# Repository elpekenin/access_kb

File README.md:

---
⚠️ _This file contains some icons that should render on GitHub, but **don't worry!** if they don't_

📝 While all the source and documentation I've developed is written on English, the report is on Spanish to be presented at my University, I might translate it on the future

---

Access keyboard
===============
This project's goal is to make a highly customizable keyboard with a bunch of accessibility add-ons, so that **most** people can use it.

File structure:
```
📂 access_kb
├─ 📂firmware/     - Code running on the keyboard, compiled using qmk_build
├─ 📂hardware/     - PCB files
|  └─ 📂libraries/     * References to KiCAD symbols and footprints 
├─ 📂software      - Client running on the PC to control the keyboard
└─ 📂typst        - Sources used to create the PDF report
```

Firmware
========
Firmware made using [QMK](https://github.com/qmk/qmk_firmware).

Code and patches can be seen on [qmk_userspace](https://github.com/elpekenin/qmk_userspace), it is built using [qmk_build](https://github.com/elpekenin/qmk_build)

Hardware
========
The PCB was designed with KiCAD, based on ***Raspberry Pi Pico*** development board, and using some symbol/footprint libraries:
- [marbastlib](https://github.com/ebastler/marbastlib) -- Keyboard parts
- [rp-pico](https://github.com/ncarandini/KiCad-RP-Pico/) -- Raspberry Pi Pico
- [custom](./hardware/libraries/my_components.pretty/)
   - Screen models based on 1xN female 2.54mm pin connectors + roughly measured rectangles. Used for placing and sizing, not used in final model
   - Symbol for MC74HC589ADR2G, footprint is just a 16-pin SOIC

Features:
- Split
- Ortholinear
- Shift registers to reduce the pins needed
  - PISO for matrix scanning
  - SIPO for control signals
- Unused GPIO's are broken out so they be used too
- e-Ink display to show the current configuration

Software 
========
Program using [Vue](https://vuejs.org/) and [Tauri](https://tauri.app/) on your computer, that can control some features of the keyboard and send information. Based on [KarlK90's work](https://github.com/qmk/qmk_xap)

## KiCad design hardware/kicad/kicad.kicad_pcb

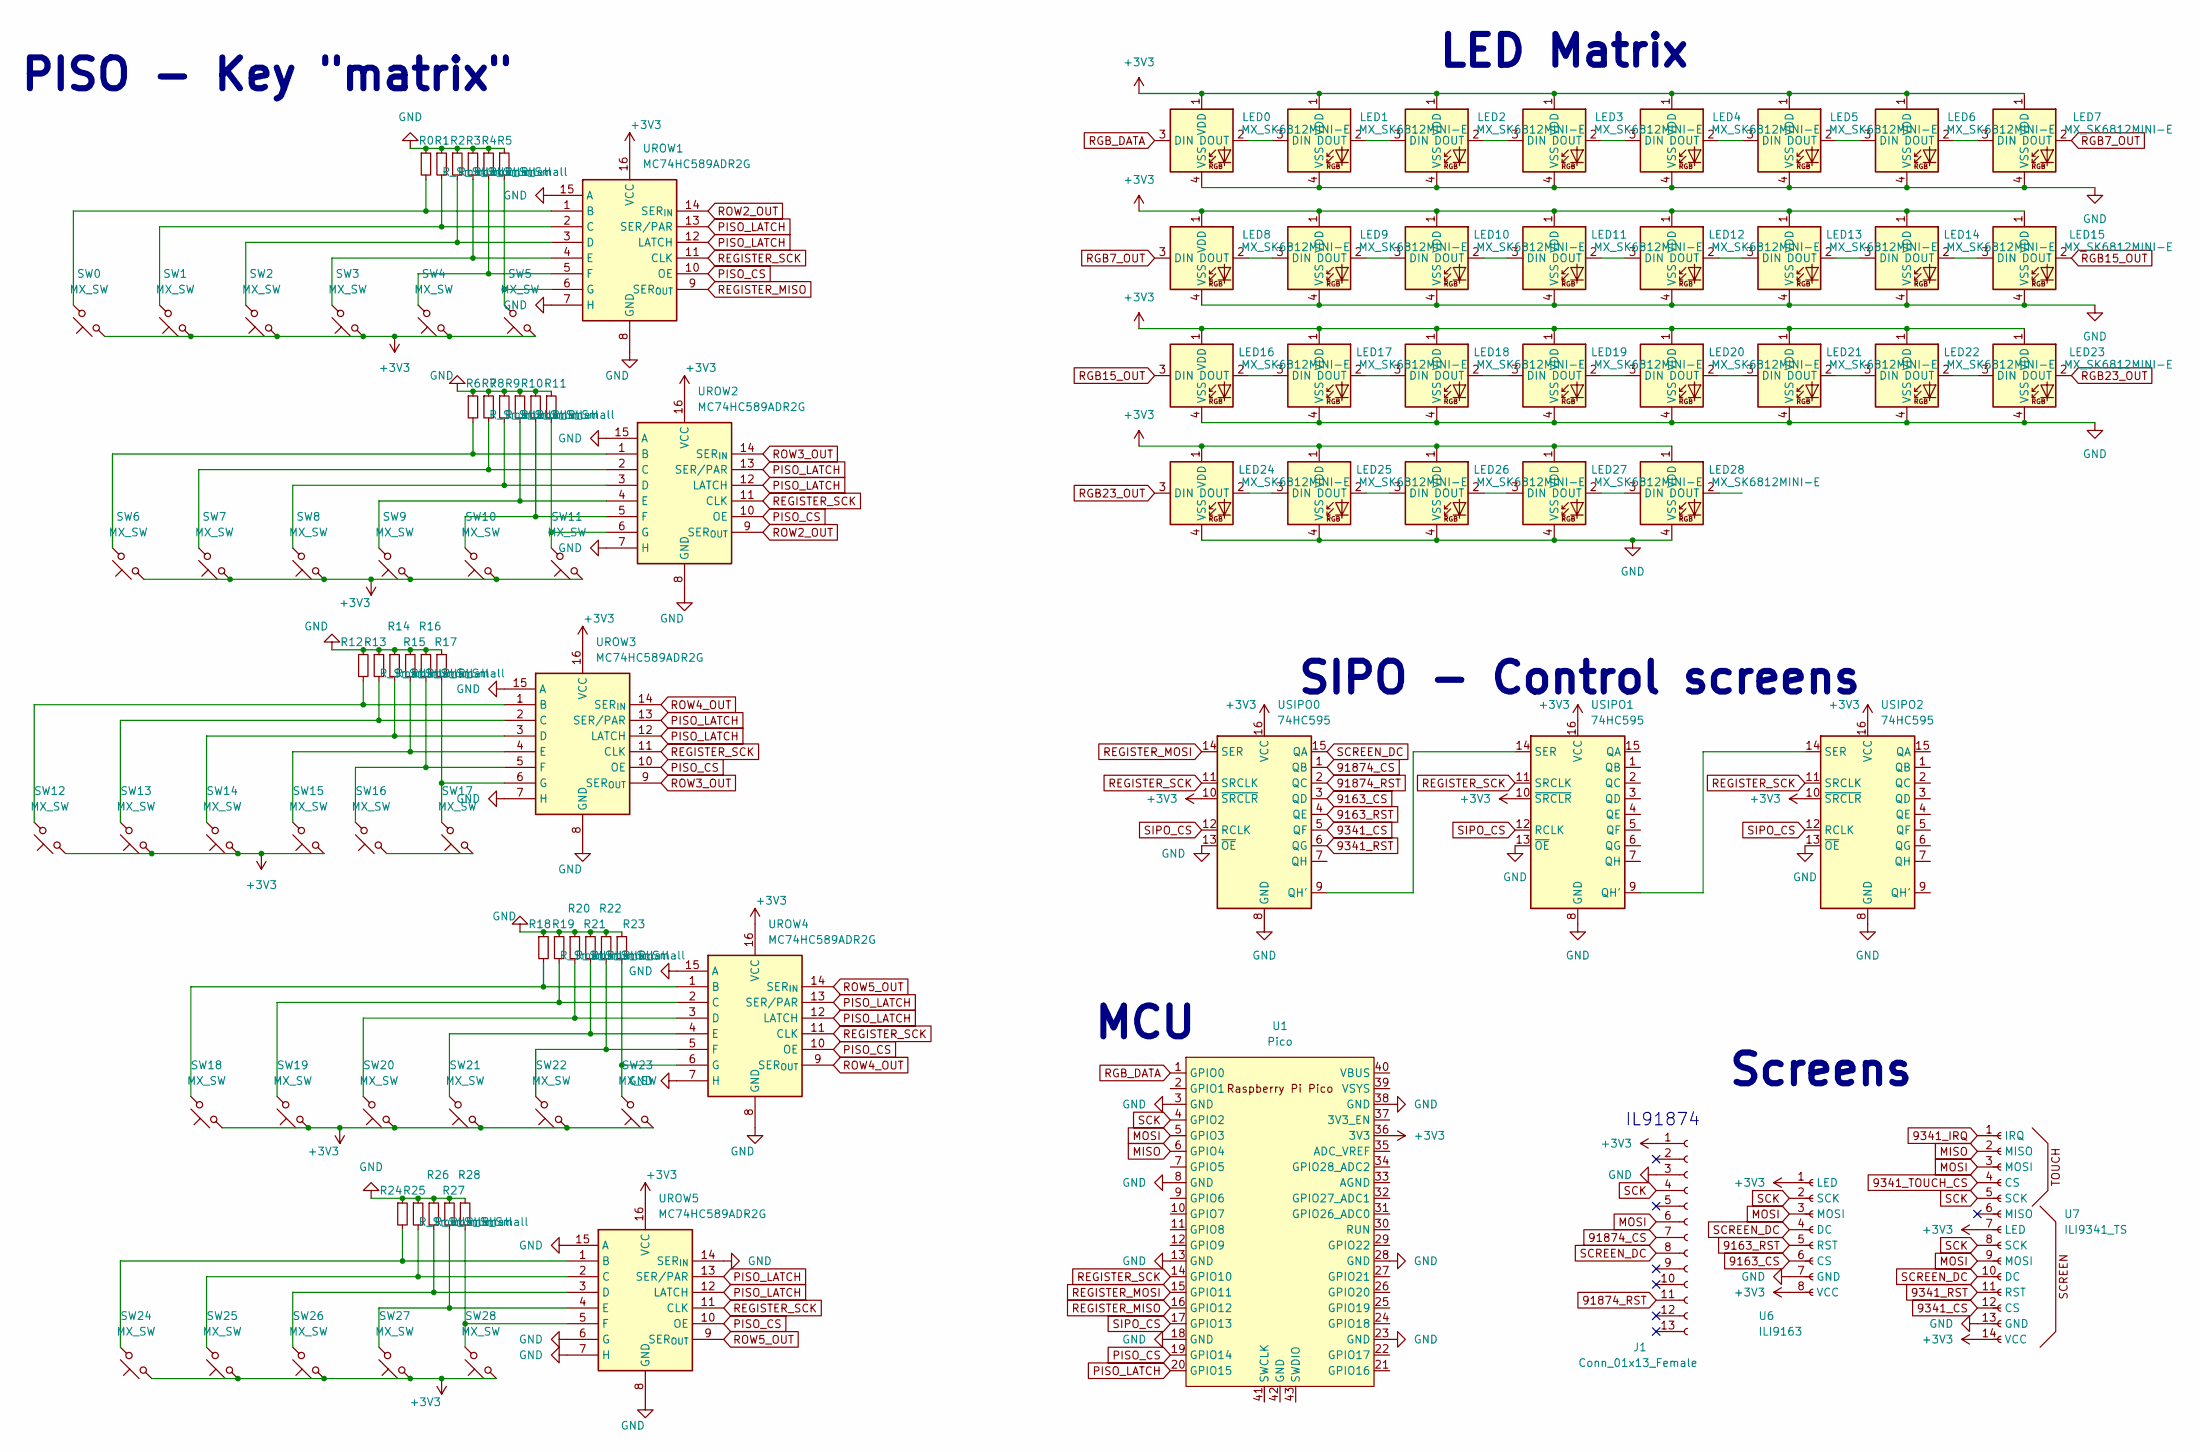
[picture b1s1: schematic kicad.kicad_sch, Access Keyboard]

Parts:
J1: Conn_01x13_Female; PinHeader_1x13_P1.00mm_Vertical
LED0, LED1, LED2, LED3, LED4, LED5, LED6, LED7, LED8, LED9, LED10, LED11, LED12, LED13, LED14, LED15, LED16, LED17, LED18, LED19, LED20, LED21, LED22, LED23, LED24, LED25, LED26, LED27, LED28: MX_SK6812MINI-E; LED_MX_6028R
R0, R1, R2, R3, R4, R5, R6, R7, R8, R9, R10, R11, R12, R13, R14, R15, R16, R17, R18, R19, R20, R21, R22, R23, R24, R25, R26, R27, R28: R_Small; R_1206_3216Metric_Pad1.30x1.75mm_HandSolder
SW0, SW1, SW2, SW3, SW4, SW5, SW6, SW7, SW8, SW9, SW10, SW11, SW12, SW13, SW14, SW15, SW16, SW17, SW18, SW19, SW20, SW21, SW22, SW23, SW24, SW25, SW26, SW27, SW28: MX_SW; SW_MX_1u
U1: Pico; RPi_Pico_SMD_TH
U6: ILI9163
U7: ILI9341_TS
UROW1, UROW2, UROW3, UROW4, UROW5: MC74HC589ADR2G; SO-16_3.9x9.9mm_P1.27mm
USIPO0, USIPO1, USIPO2: 74HC595; SO-16_3.9x9.9mm_P1.27mm

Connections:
9163_CS: U6.6 (CS), USIPO0.3 (QD)
9163_RST: U6.5 (RST), USIPO0.4 (QE)
9341_CS: U7.12 (CS), USIPO0.5 (QF)
9341_IRQ: U7.1 (IRQ)
9341_RST: U7.11 (RST), USIPO0.6 (QG)
9341_TOUCH_CS: U7.4 (CS)
91874_CS: J1.7, USIPO0.1 (QB)
91874_RST: J1.11, USIPO0.2 (QC)
+3V3: J1.1, LED0.1 (VDD), LED1.1 (VDD), LED2.1 (VDD), LED3.1 (VDD), LED4.1 (VDD), LED5.1 (VDD), LED6.1 (VDD), LED7.1 (VDD), LED8.1 (VDD), LED9.1 (VDD), LED10.1 (VDD), LED11.1 (VDD), LED12.1 (VDD), LED13.1 (VDD), LED14.1 (VDD), LED15.1 (VDD), LED16.1 (VDD), LED17.1 (VDD), LED18.1 (VDD), LED19.1 (VDD), LED20.1 (VDD), LED21.1 (VDD), LED22.1 (VDD), LED23.1 (VDD), LED24.1 (VDD), LED25.1 (VDD), LED26.1 (VDD), LED27.1 (VDD), LED28.1 (VDD), SW0.1, SW1.1, SW2.1, SW3.1, SW4.1, SW5.1, SW6.1, SW7.1, SW8.1, SW9.1, SW10.1, SW11.1, SW12.1, SW13.1, SW14.1, SW15.1, SW18.1, SW19.1, SW20.1, SW21.1, SW22.1, SW23.1, SW24.1, SW25.1, SW26.1, SW27.1, SW28.1, U1.36 (3V3), U6.1 (LED), U6.8 (VCC), U7.7 (LED), U7.14 (VCC), UROW1.16 (VCC), UROW2.16 (VCC), UROW3.16 (VCC), UROW4.16 (VCC), UROW5.16 (VCC), USIPO0.10 (~SRCLR), USIPO0.16 (VCC), USIPO1.10 (~SRCLR), USIPO1.16 (VCC), USIPO2.10 (~SRCLR), USIPO2.16 (VCC)
GND: J1.3, LED0.4 (VSS), LED1.4 (VSS), LED2.4 (VSS), LED3.4 (VSS), LED4.4 (VSS), LED5.4 (VSS), LED6.4 (VSS), LED7.4 (VSS), LED8.4 (VSS), LED9.4 (VSS), LED10.4 (VSS), LED11.4 (VSS), LED12.4 (VSS), LED13.4 (VSS), LED14.4 (VSS), LED15.4 (VSS), LED16.4 (VSS), LED17.4 (VSS), LED18.4 (VSS), LED19.4 (VSS), LED20.4 (VSS), LED21.4 (VSS), LED22.4 (VSS), LED23.4 (VSS), LED24.4 (VSS), LED25.4 (VSS), LED26.4 (VSS), LED27.4 (VSS), LED28.4 (VSS), R0.1, R1.1, R2.1, R3.1, R4.1, R5.1, R6.1, R7.1, R8.1, R9.1, R10.1, R11.1, R12.1, R13.1, R14.1, R15.1, R16.1, R17.1, R18.1, R19.1, R20.1, R21.1, R22.1, R23.1, R24.1, R25.1, R26.1, R27.1, R28.1, U1.3 (GND), U1.8 (GND), U1.13 (GND), U1.18 (GND), U1.23 (GND), U1.28 (GND), U1.38 (GND), U6.7 (GND), U7.13 (GND), UROW1.7 (H), UROW1.8 (GND), UROW1.15 (A), UROW2.7 (H), UROW2.8 (GND), UROW2.15 (A), UROW3.7 (H), UROW3.8 (GND), UROW3.15 (A), UROW4.7 (H), UROW4.8 (GND), UROW4.15 (A), UROW5.6 (G), UROW5.7 (H), UROW5.8 (GND), UROW5.14 (SER_{IN}), UROW5.15 (A), USIPO0.8 (GND), USIPO0.13 (~OE), USIPO1.8 (GND), USIPO1.13 (~OE), USIPO2.8 (GND), USIPO2.13 (~OE)
MISO: U1.6 (GPIO4), U7.2 (MISO)
MOSI: J1.6, U1.5 (GPIO3), U6.3 (MOSI), U7.3 (MOSI), U7.9 (MOSI)
unnamed: LED0.2 (DOUT), LED1.3 (DIN)
unnamed: LED1.2 (DOUT), LED2.3 (DIN)
unnamed: LED2.2 (DOUT), LED3.3 (DIN)
unnamed: LED3.2 (DOUT), LED4.3 (DIN)
unnamed: LED4.2 (DOUT), LED5.3 (DIN)
unnamed: LED5.2 (DOUT), LED6.3 (DIN)
unnamed: LED6.2 (DOUT), LED7.3 (DIN)
unnamed: LED8.2 (DOUT), LED9.3 (DIN)
unnamed: LED10.2 (DOUT), LED11.3 (DIN)
unnamed: LED9.2 (DOUT), LED10.3 (DIN)
unnamed: LED11.2 (DOUT), LED12.3 (DIN)
unnamed: LED12.2 (DOUT), LED13.3 (DIN)
unnamed: LED13.2 (DOUT), LED14.3 (DIN)
unnamed: LED14.2 (DOUT), LED15.3 (DIN)
unnamed: LED16.2 (DOUT), LED17.3 (DIN)
unnamed: LED17.2 (DOUT), LED18.3 (DIN)
unnamed: LED18.2 (DOUT), LED19.3 (DIN)
unnamed: LED19.2 (DOUT), LED20.3 (DIN)
unnamed: LED20.2 (DOUT), LED21.3 (DIN)
unnamed: LED21.2 (DOUT), LED22.3 (DIN)
unnamed: LED22.2 (DOUT), LED23.3 (DIN)
unnamed: LED24.2 (DOUT), LED25.3 (DIN)
unnamed: LED25.2 (DOUT), LED26.3 (DIN)
unnamed: LED26.2 (DOUT), LED27.3 (DIN)
unnamed: LED27.2 (DOUT), LED28.3 (DIN)
unnamed: R0.2, SW0.2, UROW1.1 (B)
unnamed: R1.2, SW1.2, UROW1.2 (C)
unnamed: R2.2, SW2.2, UROW1.3 (D)
unnamed: R3.2, SW3.2, UROW1.4 (E)
unnamed: R4.2, SW4.2, UROW1.5 (F)
unnamed: R5.2, SW5.2, UROW1.6 (G)
unnamed: R6.2, SW6.2, UROW2.1 (B)
unnamed: R7.2, SW7.2, UROW2.2 (C)
unnamed: R8.2, SW8.2, UROW2.3 (D)
unnamed: R9.2, SW9.2, UROW2.4 (E)
unnamed: R10.2, SW10.2, UROW2.5 (F)
unnamed: R11.2, SW11.2, UROW2.6 (G)
unnamed: R12.2, SW12.2, UROW3.1 (B)
unnamed: R13.2, SW13.2, UROW3.2 (C)
unnamed: R14.2, SW14.2, UROW3.3 (D)
unnamed: R15.2, SW15.2, UROW3.4 (E)
unnamed: R16.2, SW16.2, UROW3.5 (F)
unnamed: R17.2, SW17.2, UROW3.6 (G)
unnamed: R18.2, SW18.2, UROW4.1 (B)
unnamed: R19.2, SW19.2, UROW4.2 (C)
unnamed: R20.2, SW20.2, UROW4.3 (D)
unnamed: R21.2, SW21.2, UROW4.4 (E)
unnamed: R22.2, SW22.2, UROW4.5 (F)
unnamed: R23.2, SW23.2, UROW4.6 (G)
unnamed: R24.2, SW24.2, UROW5.1 (B)
unnamed: R25.2, SW25.2, UROW5.2 (C)
unnamed: R26.2, SW26.2, UROW5.3 (D)
unnamed: R27.2, SW27.2, UROW5.4 (E)
unnamed: R28.2, SW28.2, UROW5.5 (F)
unnamed: SW16.1, SW17.1
unnamed: USIPO0.9 (QH'), USIPO1.14 (SER)
unnamed: USIPO1.9 (QH'), USIPO2.14 (SER)
PISO_CS: U1.19 (GPIO14), UROW1.10 (OE), UROW2.10 (OE), UROW3.10 (OE), UROW4.10 (OE), UROW5.10 (OE)
PISO_LATCH: U1.20 (GPIO15), UROW1.12 (LATCH), UROW1.13 (SER/PAR), UROW2.12 (LATCH), UROW2.13 (SER/PAR), UROW3.12 (LATCH), UROW3.13 (SER/PAR), UROW4.12 (LATCH), UROW4.13 (SER/PAR), UROW5.12 (LATCH), UROW5.13 (SER/PAR)
REGISTER_MISO: U1.16 (GPIO12), UROW1.9 (SER_{OUT})
REGISTER_MOSI: U1.15 (GPIO11), USIPO0.14 (SER)
REGISTER_SCK: U1.14 (GPIO10), UROW1.11 (CLK), UROW2.11 (CLK), UROW3.11 (CLK), UROW4.11 (CLK), UROW5.11 (CLK), USIPO0.11 (SRCLK), USIPO1.11 (SRCLK), USIPO2.11 (SRCLK)
RGB7_OUT: LED7.2 (DOUT), LED8.3 (DIN)
RGB15_OUT: LED15.2 (DOUT), LED16.3 (DIN)
RGB23_OUT: LED23.2 (DOUT), LED24.3 (DIN)
RGB_DATA: LED0.3 (DIN), U1.1 (GPIO0)
ROW2_OUT: UROW1.14 (SER_{IN}), UROW2.9 (SER_{OUT})
ROW3_OUT: UROW2.14 (SER_{IN}), UROW3.9 (SER_{OUT})
ROW4_OUT: UROW3.14 (SER_{IN}), UROW4.9 (SER_{OUT})
ROW5_OUT: UROW4.14 (SER_{IN}), UROW5.9 (SER_{OUT})
SCK: J1.4, U1.4 (GPIO2), U6.2 (SCK), U7.5 (SCK), U7.8 (SCK)
SCREEN_DC: J1.8, U6.4 (DC), U7.10 (DC), USIPO0.15 (QA)
SIPO_CS: U1.17 (GPIO13), USIPO0.12 (RCLK), USIPO1.12 (RCLK), USIPO2.12 (RCLK)

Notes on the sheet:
LED Matrix
IL91874
SIPO - Control screens
MCU
PISO - Key "matrix"
Screens

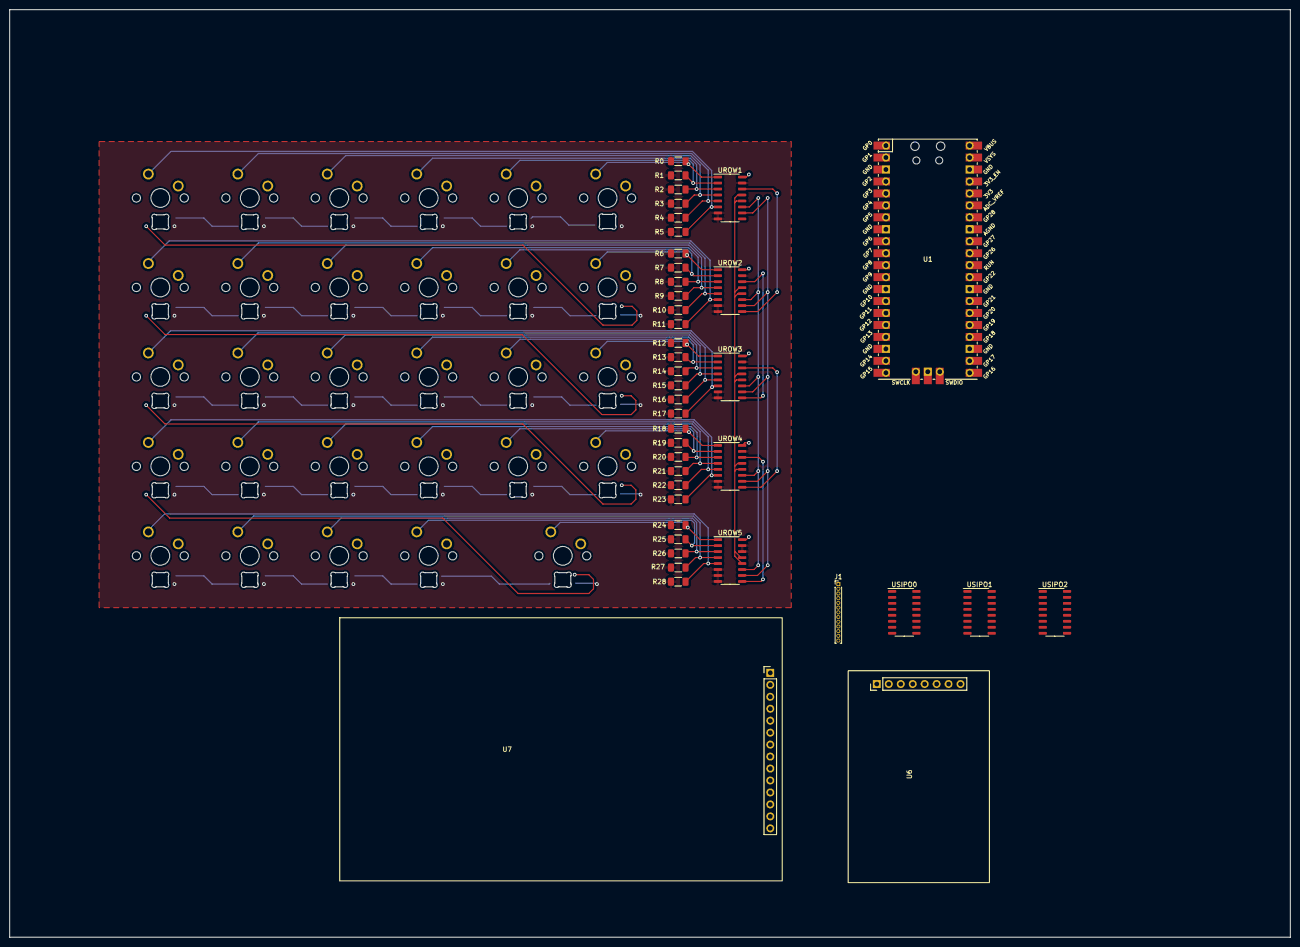
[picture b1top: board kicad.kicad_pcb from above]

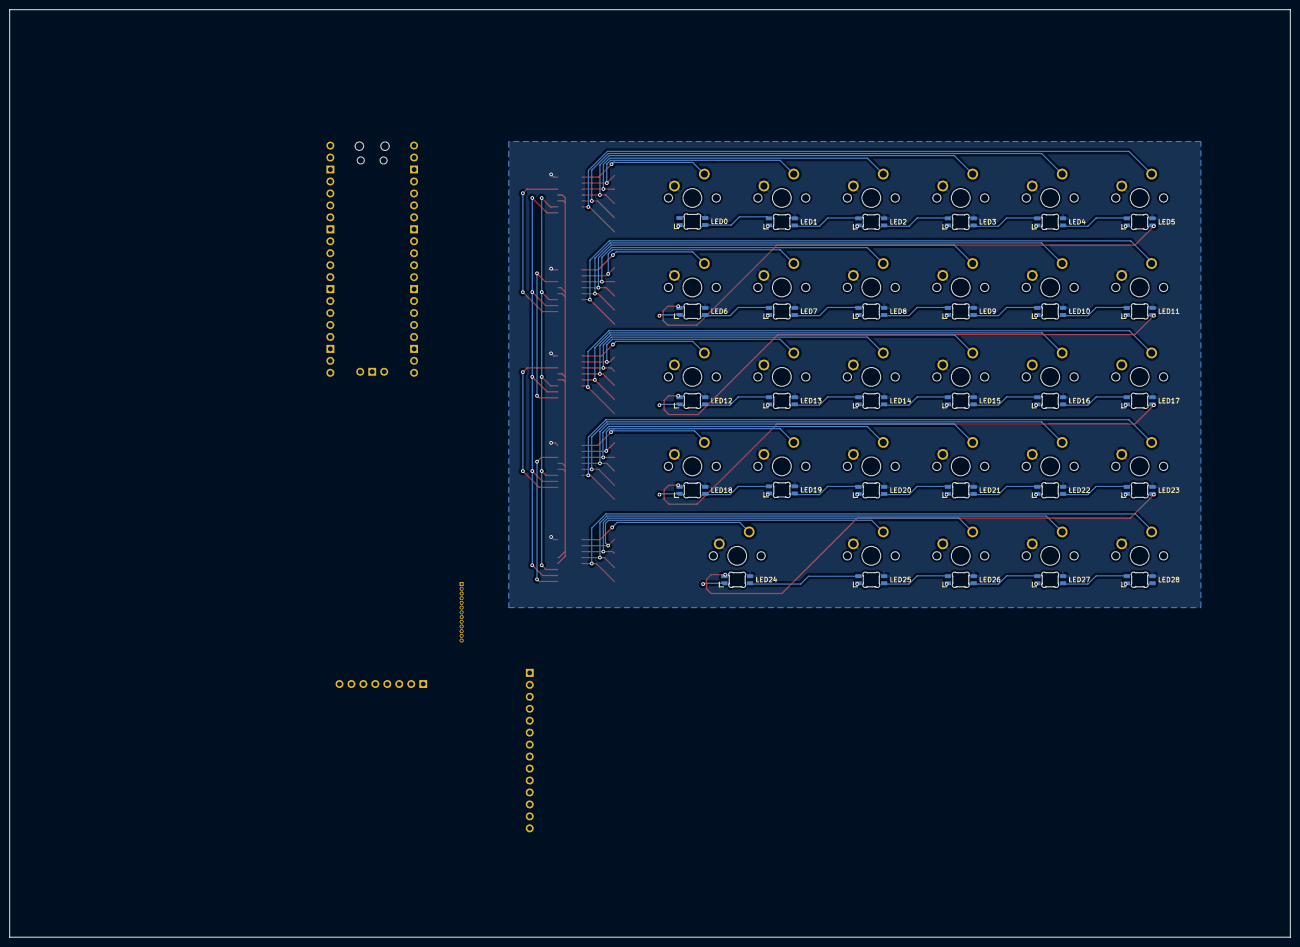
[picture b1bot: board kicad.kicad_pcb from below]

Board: 2 copper layers, 272.0 x 197.0 mm, 99 parts (58 on the bottom side), 83 nets.

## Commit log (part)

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2022-08-23 Added submodules
2022-08-23 Initial README
2022-08-23 Moving to forked submodules
2022-08-23 Added forked submodules
2022-08-23 Added LaTeX file structure and updated README
2022-08-24 Some progress on the report
2022-08-24 readme wasnt updated...
2022-08-25 Readme progress & preparing for peke-devel branch on MP
2022-08-25 .gitmodules correct alignment
2022-08-25 state of the art added
2022-08-26 reverted micropython updated submodule which broke compiling
2022-08-26 removed tinyusb and little changes to report
2022-08-26 update micropython fork to messy-hid commit
2022-08-26 remove tinyusb submodule from readme
2022-08-27 some helper functions & first uPy tests
2022-08-27 fix pdf script
2022-08-27 oops, uPy code now tracked
2022-08-27 added uploading script & renamed scripts/folders to navigate easier
2022-08-27 oops, remove old names
2022-08-28 submodules up to date
2022-08-29 update to 'working' HID commit & merge some small changes
2022-08-30 [29-8] update progress
2022-08-31 [30-8] update progress
2022-09-01 [1-9] update progress
2022-09-04 minor PCB changes -- RP2040+core components done (?)
2022-09-05 update README icons
2022-09-15 [16-09] added level shifter + progress on the expasion connector
2022-10-17 [18-10] Started with Tauri, and updated report
2022-10-18 [18-10] Better Tauri documentation
2022-10-18 [18-10] Upadte report
2022-10-18 [18-10] Push initial Tauri+Astro code
2022-10-18 [18-10] Delete Python code and update README
2022-10-19 [19-10] Update report & Configure Tauri's TOML
2022-10-19 [20-10] First JS->Rust MWE
2022-10-20 [20-10] Svelte MWE
2022-10-20 [20-10] Update README
2022-10-20 Add missing {}
2022-10-20 Remove useless argument
2022-10-22 Update Rust code
2022-10-22 Improve formatting
2022-10-22 Change from_data to create reports of both directions
2022-10-22 Initial From/Into implementation, WIP
2022-10-23 Update XAP code
2022-10-23 Add builder pattern & Write/Read now take a report, handle errors and log
2022-10-23 Abstract from_kb handling into write/read methods
2022-10-24 Add enum & Minor changes
2022-10-25 Rename enum, add from_route to XAPReport, create token on sending function, prevent received data to be modified
2022-10-26 Random token + Route struct
2022-10-26 Change arrays to slice, so API is friendlier
2022-10-26 Add hex literal prefix
2022-10-26 Change bool to u8, it still uses a bit, but easier to work with
2022-11-01 [1-11] Change my Astro implementation for Karl's fork
2022-11-29 QMK progress added
2022-11-30 Add software progress
2023-01-29 Update PCB
2023-01-30 Matrix wired
2023-01-30 Add missing row5 to row4 chain
2023-02-02 Second half added
2023-02-02 Breakout connectors left
2023-02-07 Done?
2023-02-07 Add capacitors, fix vias in pads and add SIPO connector
2023-02-08 Minimal changes
2023-02-14 Update XAPClient
2023-02-21 Fix label & Add gerbers
2023-03-20 Some progress
2023-05-17 Update GitHub
2023-11-14 Add firmware files
2023-11-14 Implement logging levels
2023-11-16 Implement `logging(FEAT, LEVEL, fmt, ...)`
2023-11-16 Use $USERSPACE + minor changes
2023-11-18 cleanup logging + split backend
2023-11-21 Split-log code togeter + sync EE_CLR + EE test + set_logging_fmt bugfix
2023-11-30 Remove EE test, add game + RNG feats
2023-12-01 Update build script
2023-12-03 `dest` -> `destination`
2023-12-08 Add `LOG_*` preffix
2023-12-10 Fix `#include`s, use `debug_config.enable`, add `debug` to scripts, RTC
2023-12-11 Change `generated` filename/include, dedicated utils folder, move ttf
2023-12-12 Implement naive hash-map
2023-12-12 Fix typo? it worked somehow anyway ha!
2023-12-13 Move to `src` and `include`
2023-12-13 Include cleanups
2023-12-14 Better hash func Use hashmap for keylog Clean `keylog.h` Explicit `NULL` checks, instead of `if(!value)` / `if(value)` Fix typo: `let's` -> `lets`
2023-12-15 Remove `ONE_HAND`, cleanup, use setters instead of `extern`
2023-12-15 Update readme, normalize comments, fix typo on `_load_font`
2023-12-19 Remove comments after `#endif` Lint `info.json` Enable bootmagic Remove `ONE_HAND` feature Cleanup `access.h` mess Tweak `matrix.c` `defer_exec` over manual timers Remove `extern` vars, use setters/i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
2023-12-19 `logging/backends/split` seems 100% correct now Add some debug helpers to `logging.h` Functions on `utils/string` now return a pointer for convenience Cleanup `build_info_t` leftovers
2023-12-25 Correct XAP payload len for string, add `WITHOUT_DEBUG` macro, minor cleanup
2023-12-28 Add some needed includes, simplify keylog
2023-12-30 Remove un-used function, silence RGBMatrix keycodes
2024-01-01 Rename `SCROLL`, add alloc tracker, cleanup `graphics.c` duplication
2024-01-01 Fix couple typos, improve format
2024-01-01 Better usage msg
2024-01-04 Multi-dict autocorrect
2024-01-07 [BROKEN] PicoSDK wrappers
2024-01-07 Path handling for MSYS
2024-01-09 Backtrace + `qmk lint`
2024-01-11 Print stack trace after crash
2024-01-11 Oops
2024-01-18 Some updates, SDK still broken
2024-01-18 SDK wrappers working finally :)
2024-01-24 Remake map with dyn-arrays
2024-01-27 Friendlier `map`(with cursed macros) and glitch text animation for heap stats
2024-02-03 Push glitch text animation
2024-02-10 Indicator for custom keycodes on `_RST` layer
2024-02-14 Better keycode extraction
2024-02-20 Remove patch for merged PR, add CI, remove $env from `build.json`
2024-02-20 (CI) Align version info
2024-02-21 (CI) Speed up?
2024-02-21 (CI) Change trigger time, run twice a day
2024-03-19 Initial -> rewrite
2024-03-19 Bitmask for indicators, refactor some macros into inline funcs, custom init section, initial code for XAP over split, disable (currently broken) multibank autocorrect
2024-03-27 init/deinit system, named macro va-args, some logging refactor
2024-04-12 several changes
2024-04-12 refactor: `bool` as success indicator -> `int`(errno) codes
2024-04-16 simplify build, *try* and use core1 for some tasks
2024-04-17 fix crash to to un-initialized timer & prevent spi deadlocking
2024-04-21 fix GHA?, better errors
2024-04-21 move matrix to core1, draw a gif from it too
2024-05-19 fix compile against QMK, minor core-related changes
2024-06-05 Fix patch after `GC9107` merge
2024-07-14 Several updates (partially? broken) * `WARN_UNUSED` in `logging` * Remove hacky `load_*` macros, force writing names * Migrate some code from C to zig * Shorter keycode names * Fix `halconf.h` order 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
2024-08-13 remove hacky macros, some C linting, break zig into modules, overrides instrospection, WIP asset fetching from `build.zig`
2024-08-19 fix build in CI/CD, change period of compilation to daily
2024-08-26 move firmware to own repo
2024-10-10 update to typst 0.11, break into smaller files, some progress
2024-10-14 [pre-commit.ci] pre-commit autoupdate
    updates:
    - [github.com/pre-commit/pre-commit-hooks: v4.6.0 → v5.0.0](https://github.com/pre-commit/pre-commit-hooks/compare/v4.6.0...v5.0.0)
2024-10-14 [pre-commit.ci] auto fixes from pre-commit.com hooks
    for more information, see https://pre-commit.ci
2024-10-15 [pre-commit.ci] pre-commit autoupdate (#1)
    * [pre-commit.ci] pre-commit autoupdate
    updates:
    - [github.com/pre-commit/pre-commit-hooks: v4.6.0 → v5.0.0](https://github.com/pre-commit/pre-commit-hooks/compare/v4.6.0...v5.0.0)
    * [pre-commit.ci] auto fixes from pre-commit.com hooks
    for more information, see https://pre-commit.ci
    ---------
2024-10-21 [pre-commit.ci] pre-commit autoupdate
    updates:
    - [github.com/Enter-tainer/typstyle: v0.11.35 → v0.12.0](https://github.com/Enter-tainer/typstyle/compare/v0.11.35...v0.12.0)
2024-10-30 [pre-commit.ci] pre-commit autoupdate (#2)
    updates:
    - [github.com/Enter-tainer/typstyle: v0.11.35 → v0.12.0](https://github.com/Enter-tainer/typstyle/compare/v0.11.35...v0.12.0)
2024-12-03 [pre-commit.ci] pre-commit autoupdate
    updates:
    - [github.com/Enter-tainer/typstyle: v0.12.0 → v0.12.6](https://github.com/Enter-tainer/typstyle/compare/v0.12.0...v0.12.6)
2024-12-09 [pre-commit.ci] pre-commit autoupdate
    updates:
    - [github.com/Enter-tainer/typstyle: v0.12.0 → v0.12.9](https://github.com/Enter-tainer/typstyle/compare/v0.12.0...v0.12.9)
2024-12-16 [pre-commit.ci] pre-commit autoupdate
    updates:
    - [github.com/Enter-tainer/typstyle: v0.12.0 → v0.12.12](https://github.com/Enter-tainer/typstyle/compare/v0.12.0...v0.12.12)
2025-03-31 [pre-commit.ci] pre-commit autoupdate
    updates:
    - [github.com/Enter-tainer/typstyle: v0.12.0 → v0.13.2](https://github.com/Enter-tainer/typstyle/compare/v0.12.0...v0.13.2)
2025-04-08 [pre-commit.ci] pre-commit autoupdate (#3)
    updates:
    - [github.com/Enter-tainer/typstyle: v0.12.0 → v0.13.2](https://github.com/Enter-tainer/typstyle/compare/v0.12.0...v0.13.2)
2025-05-19 [pre-commit.ci] pre-commit autoupdate
    updates:
    - [github.com/Enter-tainer/typstyle: v0.13.2 → v0.13.7](https://github.com/Enter-tainer/typstyle/compare/v0.13.2...v0.13.7)
2025-05-19 [WIP] more (re)writing
2025-05-26 first draft
2026-05-14 further writing state-of-art and firmware
    remove `hydra` dependency
    use utility for section nesting
    add acknowledgements
    `tinymist` config for vscode
    remove dangling refs from bibliography
2026-05-24 state of the art and hardware finished (?)
2026-05-25 [pre-commit.ci] pre-commit autoupdate
    updates:
    - [github.com/pre-commit/pre-commit-hooks: v5.0.0 → v6.0.0](https://github.com/pre-commit/pre-commit-hooks/compare/v5.0.0...v6.0.0)
2026-05-26 v1-rc0
2026-05-26 [pre-commit.ci] pre-commit autoupdate (#4)
    updates:
    - [github.com/pre-commit/pre-commit-hooks: v5.0.0 → v6.0.0](https://github.com/pre-commit/pre-commit-hooks/compare/v5.0.0...v6.0.0)
2026-05-26 v1-rc1
2026-06-16 chore: remove outdated README
2026-06-21 feat: add m5 integration
